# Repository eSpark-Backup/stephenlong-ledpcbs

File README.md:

# Direct Drive and Full Circuit LED Proto PCBAs
#### Client Name: Stephen Long Jr.

## Project Requirements
Refer to 2x2 design pushed in docs folder and carry out below requirements (the 2x2 design probably references more to the Full Circuit LED Proto PCBA)

### Full Circuit LED Proto PCBA
- Spaced 10mm center to center.
- Arranged in a 2 wide, 3 high grid.  

- UCS 7604 constant-current driver IC
- Required resistors, capacitors, and other supporting circuitry.
- Voltage VDD, GND, and data input/output lines will terminate in accessible solder pads for easy interfacing.
- The board should allow user to have both direct drive and full circuit capabilities by the following approach:
    - run each positive and negative pad to a row of jumpers, each LED will have 3 pins on this jumper header assigned to it. The center pin will be connected to the trace for the LED pad. The left pin will be connected to the full driving circuit with IC. The right pin will go directly to a solder pad. This sequence will happen for each led (x12), then:
        - **For Direct Drive:** User would put all the jumpers over to the center and right pin, then solder wires to the solder pads.
        - **For Full Circuit:** User would put all of the jumpers on the left and center pin for each LED.
- 4 x mounting holes for M3 screw clearance.

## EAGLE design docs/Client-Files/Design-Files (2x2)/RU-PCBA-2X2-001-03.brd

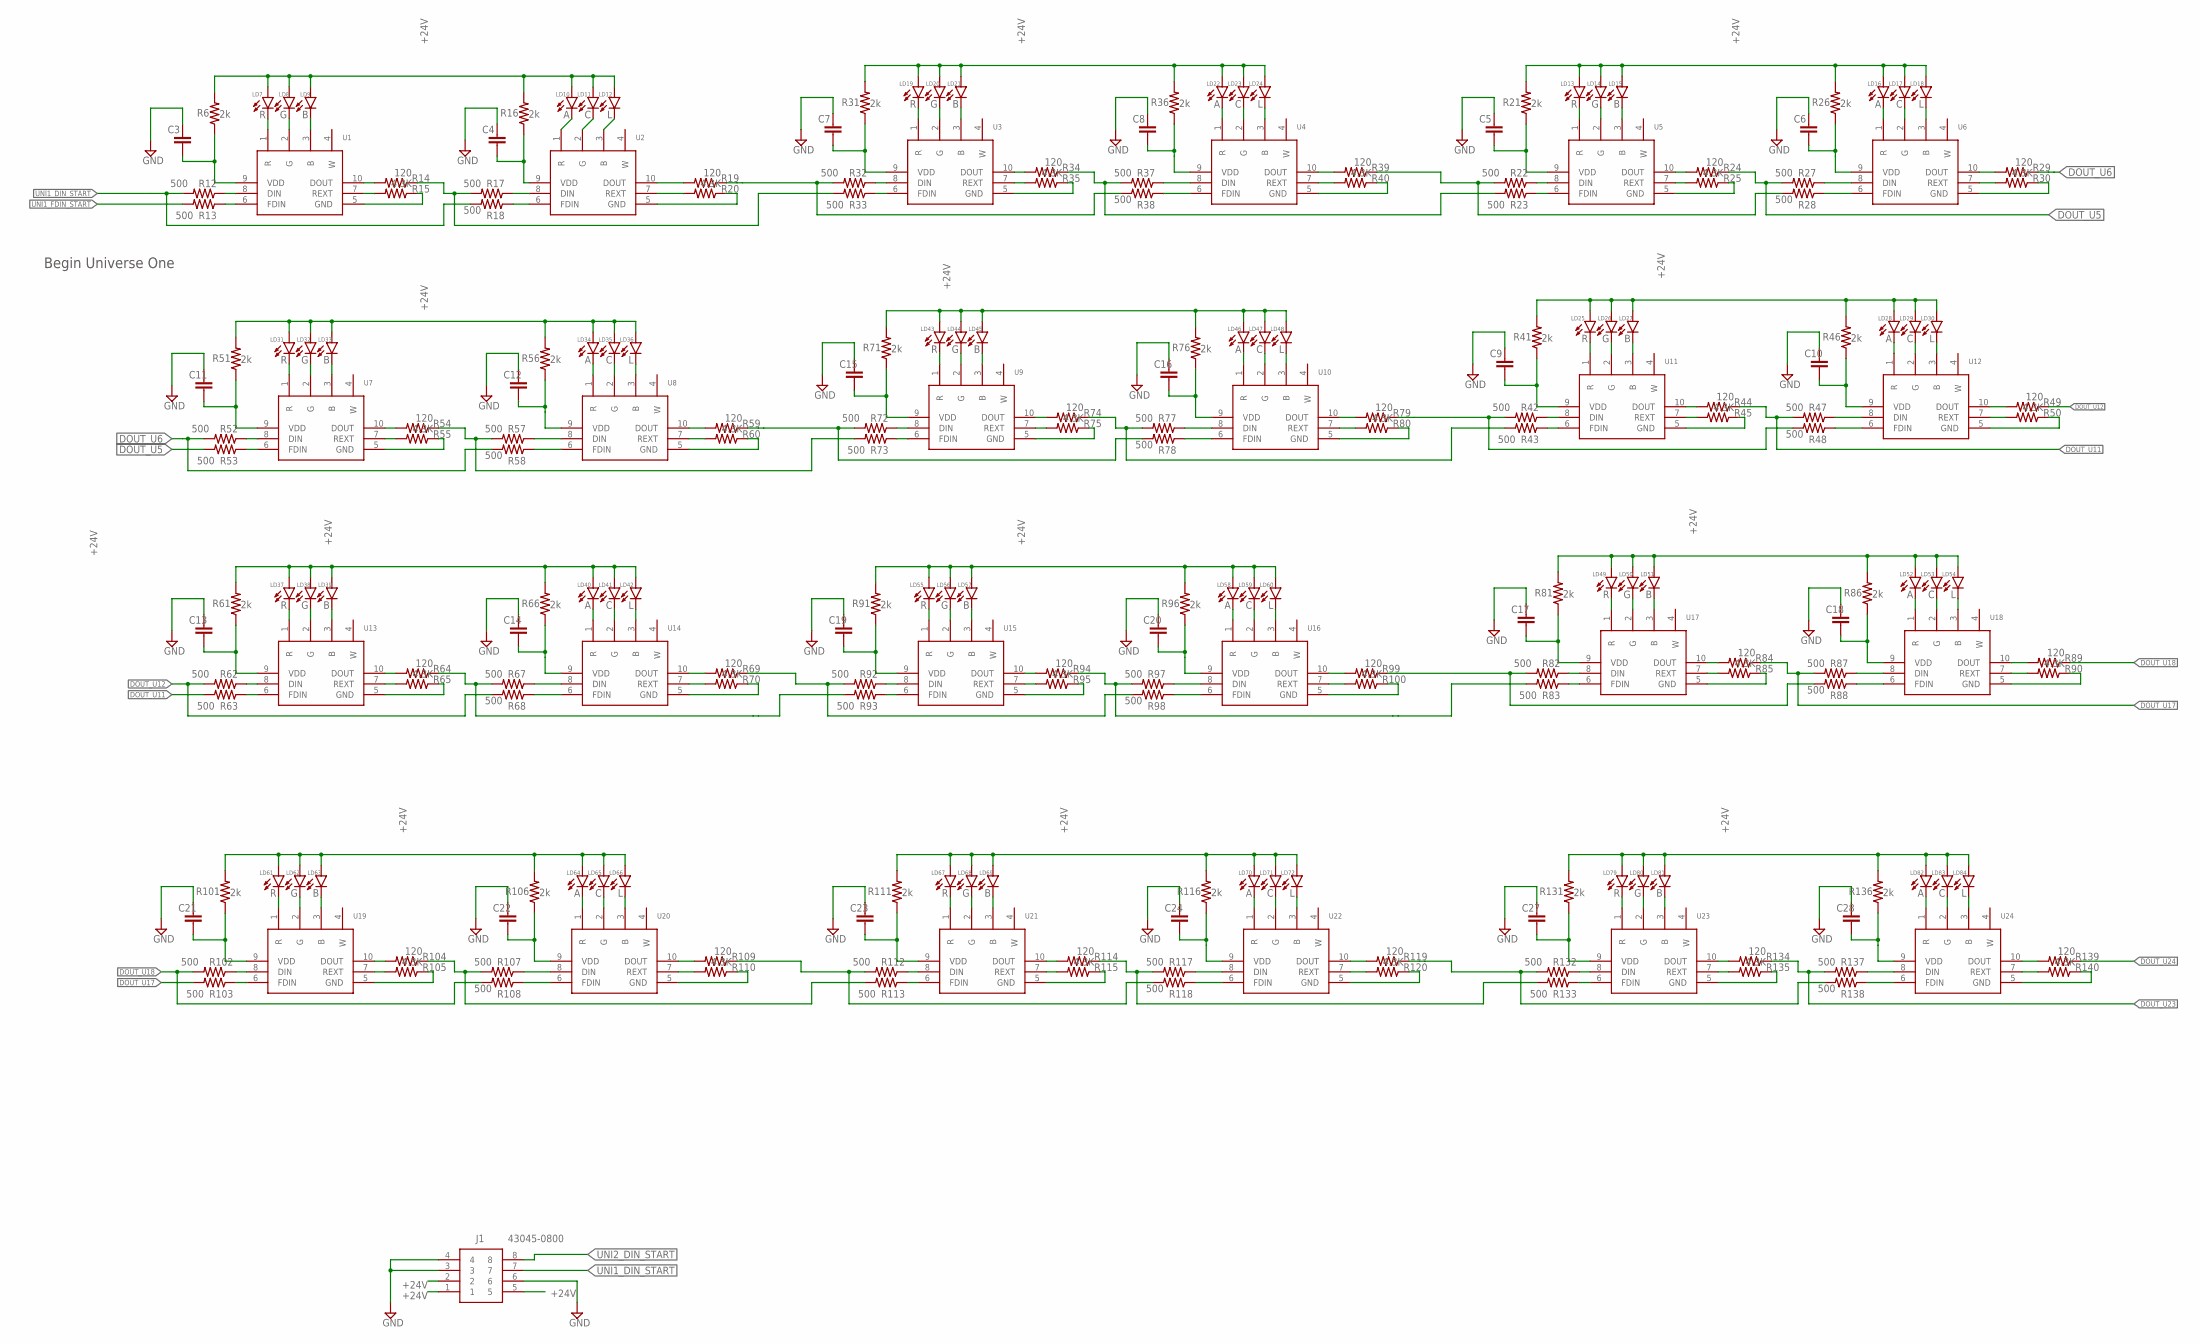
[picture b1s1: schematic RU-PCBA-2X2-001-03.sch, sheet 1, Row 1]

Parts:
C3, C4, C5, C6, C7, C8, C9, C10, C11, C12, C13, C14, C15, C16, C17, C18, C19, C20, C21, C22, C23, C24, C27, C28: C-EUC1206; C1206; MPN C_104
J1: 43045-0800; 43045-08(00,01,02,10)
LD7, LD13, LD19, LD25, LD31, LD37, LD43, LD49, LD55, LD61, LD67, LD79: R; 5050LED; MPN R_5050
LD8, LD14, LD20, LD26, LD32, LD38, LD44, LD50, LD56, LD62, LD68, LD80: G; 5050LED; MPN G_5050
LD9, LD15, LD21, LD27, LD33, LD39, LD45, LD51, LD57, LD63, LD69, LD81: B; 5050LED; MPN B_5050
LD10, LD16, LD22, LD28, LD34, LD40, LD46, LD52, LD58, LD64, LD70, LD82: A; 5050LED; MPN A_5050
LD11, LD17, LD23, LD29, LD35, LD41, LD47, LD53, LD59, LD65, LD71, LD83: C; 5050LED; MPN C_5050
LD12, LD18, LD24, LD30, LD36, LD42, LD48, LD54, LD60, LD66, LD72, LD84: L; 5050LED; MPN L_5050
R6, R16, R21, R26, R31, R36, R41, R46, R51, R56, R61, R66, R71, R76, R81, R86, R91, R96, R101, R106, R111, R116, R131, R136: 2k; R1206; MPN R_VDD
R12, R13, R17, R18, R22, R23, R27, R28, R32, R33, R37, R38, R42, R43, R47, R48, R52, R53, R57, R58, R62, R63, R67, R68, R72, R73, R77, R78, R82, R83, R87, R88, R92, R93, R97, R98, R102, R103, R107, R108, R112, R113, R117, R118, R132, R133, R137, R138: 500; R0805; MPN R_500
R14, R19, R24, R29, R34, R39, R44, R49, R54, R59, R64, R69, R74, R79, R84, R89, R94, R99, R104, R109, R114, R119, R134, R139: 120; R0805; MPN R_120
R15, R20, R25, R30, R35, R40, R45, R50, R55, R60, R65, R70, R75, R80, R85, R90, R95, R100, R105, R110, R115, R120, R135, R140: 4.3K; R0805; MPN R_EXT
U1, U2, U3, U4, U5, U6, U7, U8, U9, U10, U11, U12, U13, U14, U15, U16, U17, U18, U19, U20, U21, U22, U23, U24: UCS7604; SOP100P600X175-10N; MPN UCS7604

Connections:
+24V: J1.1, J1.2, J1.5, LD7.A, LD8.A, LD9.A, LD10.A, LD11.A, LD12.A, LD13.A, LD14.A, LD15.A, LD16.A, LD17.A, LD18.A, LD19.A, LD20.A, LD21.A, LD22.A, LD23.A, LD24.A, LD25.A, LD26.A, LD27.A, LD28.A, LD29.A, LD30.A, LD31.A, LD32.A, LD33.A, LD34.A, LD35.A, LD36.A, LD37.A, LD38.A, LD39.A, LD40.A, LD41.A, LD42.A, LD43.A, LD44.A, LD45.A, LD46.A, LD47.A, LD48.A, LD49.A, LD50.A, LD51.A, LD52.A, LD53.A, LD54.A, LD55.A, LD56.A, LD57.A, LD58.A, LD59.A, LD60.A, LD61.A, LD62.A, LD63.A, LD64.A, LD65.A, LD66.A, LD67.A, LD68.A, LD69.A, LD70.A, LD71.A, LD72.A, LD79.A, LD80.A, LD81.A, LD82.A, LD83.A, LD84.A, R6.2, R16.2, R21.2, R26.2, R31.2, R36.2, R41.2, R46.2, R51.2, R56.2, R61.2, R66.2, R71.2, R76.2, R81.2, R86.2, R91.2, R96.2, R101.2, R106.2, R111.2, R116.2, R131.2, R136.2; also elsewhere on the board
DOUT_U5: R24.1, R27.2, R53.2
DOUT_U6: R29.1, R52.2, R58.2
DOUT_U11: R44.1, R47.2, R63.2
DOUT_U12: R49.1, R62.2, R68.2
DOUT_U17: R84.1, R87.2, R103.2
DOUT_U18: R89.1, R102.2, R108.2
DOUT_U23: R134.1, R137.2; also elsewhere on the board
DOUT_U24: R139.1; also elsewhere on the board
GND: C3.2, C4.2, C5.2, C6.2, C7.2, C8.2, C9.2, C10.2, C11.2, C12.2, C13.2, C14.2, C15.2, C16.2, C17.2, C18.2, C19.2, C20.2, C21.2, C22.2, C23.2, C24.2, C27.2, C28.2, J1.3, J1.4, J1.6, R15.1, R20.1, R25.1, R30.1, R35.1, R40.1, R45.1, R50.1, R55.1, R60.1, R65.1, R70.1, R75.1, R80.1, R85.1, R90.1, R95.1, R100.1, R105.1, R110.1, R115.1, R120.1, R135.1, R140.1, U1.5 (GND), U2.5 (GND), U3.5 (GND), U4.5 (GND), U5.5 (GND), U6.5 (GND), U7.5 (GND), U8.5 (GND), U9.5 (GND), U10.5 (GND), U11.5 (GND), U12.5 (GND), U13.5 (GND), U14.5 (GND), U15.5 (GND), U16.5 (GND), U17.5 (GND), U18.5 (GND), U19.5 (GND), U20.5 (GND), U21.5 (GND), U22.5 (GND), U23.5 (GND), U24.5 (GND); also elsewhere on the board
unnamed: C3.1, R6.1, U1.9 (VDD)
unnamed: LD7.K (C), U1.1 (R)
unnamed: LD8.K (C), U1.2 (G)
unnamed: LD9.K (C), U1.3 (B)
unnamed: R12.1, U1.8 (DIN)
unnamed: R13.1, U1.6 (FDIN)
unnamed: R14.2, U1.10 (DOUT)
unnamed: R15.2, U1.7 (REXT)
unnamed: LD10.K (C), U2.1 (R)
unnamed: LD11.K (C), U2.2 (G)
unnamed: LD12.K (C), U2.3 (B)
unnamed: C4.1, R16.1, U2.9 (VDD)
unnamed: R17.1, U2.8 (DIN)
unnamed: R18.1, U2.6 (FDIN)
unnamed: R19.2, U2.10 (DOUT)
unnamed: R20.2, U2.7 (REXT)
unnamed: R19.1, R32.2, R38.2
unnamed: C5.1, R21.1, U5.9 (VDD)
unnamed: LD13.K (C), U5.1 (R)
unnamed: LD14.K (C), U5.2 (G)
unnamed: LD15.K (C), U5.3 (B)
unnamed: R22.1, U5.8 (DIN)
unnamed: R23.1, U5.6 (FDIN)
unnamed: R24.2, U5.10 (DOUT)
unnamed: R25.2, U5.7 (REXT)
unnamed: LD16.K (C), U6.1 (R)
unnamed: LD17.K (C), U6.2 (G)
unnamed: LD18.K (C), U6.3 (B)
unnamed: C6.1, R26.1, U6.9 (VDD)
unnamed: R27.1, U6.8 (DIN)
unnamed: R28.1, U6.6 (FDIN)
unnamed: R29.2, U6.10 (DOUT)
unnamed: R30.2, U6.7 (REXT)
unnamed: C7.1, R31.1, U3.9 (VDD)
unnamed: LD19.K (C), U3.1 (R)
unnamed: LD20.K (C), U3.2 (G)
unnamed: LD21.K (C), U3.3 (B)
unnamed: R32.1, U3.8 (DIN)
unnamed: R33.1, U3.6 (FDIN)
unnamed: R34.2, U3.10 (DOUT)
unnamed: R35.2, U3.7 (REXT)
unnamed: LD22.K (C), U4.1 (R)
unnamed: LD23.K (C), U4.2 (G)
unnamed: LD24.K (C), U4.3 (B)
unnamed: C8.1, R36.1, U4.9 (VDD)
unnamed: R37.1, U4.8 (DIN)
unnamed: R23.2, R34.1, R37.2
unnamed: R38.1, U4.6 (FDIN)
unnamed: R14.1, R17.2, R33.2
unnamed: R39.2, U4.10 (DOUT)
unnamed: R40.2, U4.7 (REXT)
unnamed: R22.2, R28.2, R39.1
unnamed: C9.1, R41.1, U11.9 (VDD)
unnamed: LD25.K (C), U11.1 (R)
unnamed: LD26.K (C), U11.2 (G)
unnamed: LD27.K (C), U11.3 (B)
unnamed: R42.1, U11.8 (DIN)
unnamed: R43.1, U11.6 (FDIN)
unnamed: R44.2, U11.10 (DOUT)
unnamed: R45.2, U11.7 (REXT)
unnamed: LD28.K (C), U12.1 (R)
unnamed: LD29.K (C), U12.2 (G)
unnamed: LD30.K (C), U12.3 (B)
unnamed: C10.1, R46.1, U12.9 (VDD)
unnamed: R47.1, U12.8 (DIN)
unnamed: R48.1, U12.6 (FDIN)
unnamed: R49.2, U12.10 (DOUT)
unnamed: R50.2, U12.7 (REXT)
unnamed: C11.1, R51.1, U7.9 (VDD)
unnamed: LD31.K (C), U7.1 (R)
unnamed: LD32.K (C), U7.2 (G)
unnamed: LD33.K (C), U7.3 (B)
unnamed: R52.1, U7.8 (DIN)
unnamed: R53.1, U7.6 (FDIN)
unnamed: R54.2, U7.10 (DOUT)
unnamed: R55.2, U7.7 (REXT)
unnamed: LD34.K (C), U8.1 (R)
unnamed: LD35.K (C), U8.2 (G)
unnamed: LD36.K (C), U8.3 (B)
unnamed: C12.1, R56.1, U8.9 (VDD)
unnamed: R57.1, U8.8 (DIN)
unnamed: R54.1, R57.2, R73.2
unnamed: R58.1, U8.6 (FDIN)
unnamed: R59.2, U8.10 (DOUT)
unnamed: R60.2, U8.7 (REXT)
unnamed: R59.1, R72.2, R78.2
unnamed: C13.1, R61.1, U13.9 (VDD)
unnamed: LD37.K (C), U13.1 (R)
unnamed: LD38.K (C), U13.2 (G)
unnamed: LD39.K (C), U13.3 (B)
unnamed: R62.1, U13.8 (DIN)
unnamed: R63.1, U13.6 (FDIN)
unnamed: R64.2, U13.10 (DOUT)
unnamed: R65.2, U13.7 (REXT)
unnamed: LD40.K (C), U14.1 (R)
unnamed: LD41.K (C), U14.2 (G)
unnamed: LD42.K (C), U14.3 (B)
unnamed: C14.1, R66.1, U14.9 (VDD)
unnamed: R67.1, U14.8 (DIN)
unnamed: R68.1, U14.6 (FDIN)
unnamed: R69.2, U14.10 (DOUT)
unnamed: R70.2, U14.7 (REXT)
unnamed: R69.1, R92.2, R98.2
unnamed: C15.1, R71.1, U9.9 (VDD)
unnamed: LD43.K (C), U9.1 (R)
unnamed: LD44.K (C), U9.2 (G)
unnamed: LD45.K (C), U9.3 (B)
unnamed: R72.1, U9.8 (DIN)
unnamed: R73.1, U9.6 (FDIN)
unnamed: R74.2, U9.10 (DOUT)
unnamed: R75.2, U9.7 (REXT)
unnamed: LD46.K (C), U10.1 (R)
unnamed: LD47.K (C), U10.2 (G)
unnamed: LD48.K (C), U10.3 (B)
unnamed: C16.1, R76.1, U10.9 (VDD)
unnamed: R77.1, U10.8 (DIN)
unnamed: R43.2, R74.1, R77.2
unnamed: R78.1, U10.6 (FDIN)
unnamed: R79.2, U10.10 (DOUT)
unnamed: R80.2, U10.7 (REXT)
unnamed: R42.2, R48.2, R79.1
unnamed: C17.1, R81.1, U17.9 (VDD)
unnamed: LD49.K (C), U17.1 (R)
unnamed: LD50.K (C), U17.2 (G)
unnamed: LD51.K (C), U17.3 (B)
unnamed: R82.1, U17.8 (DIN)
unnamed: R83.1, U17.6 (FDIN)
unnamed: R84.2, U17.10 (DOUT)
unnamed: R85.2, U17.7 (REXT)
unnamed: LD52.K (C), U18.1 (R)
unnamed: LD53.K (C), U18.2 (G)
unnamed: LD54.K (C), U18.3 (B)
unnamed: C18.1, R86.1, U18.9 (VDD)
unnamed: R87.1, U18.8 (DIN)
unnamed: R88.1, U18.6 (FDIN)
unnamed: R82.2, R88.2, R99.1
unnamed: R83.2, R94.1, R97.2
unnamed: R89.2, U18.10 (DOUT)
unnamed: R90.2, U18.7 (REXT)
unnamed: C19.1, R91.1, U15.9 (VDD)
unnamed: LD55.K (C), U15.1 (R)
unnamed: LD56.K (C), U15.2 (G)
unnamed: LD57.K (C), U15.3 (B)
unnamed: R92.1, U15.8 (DIN)
unnamed: R93.1, U15.6 (FDIN)
unnamed: R94.2, U15.10 (DOUT)
unnamed: R95.2, U15.7 (REXT)
unnamed: LD58.K (C), U16.1 (R)
unnamed: LD59.K (C), U16.2 (G)
unnamed: LD60.K (C), U16.3 (B)
unnamed: C20.1, R96.1, U16.9 (VDD)
unnamed: R97.1, U16.8 (DIN)
unnamed: R98.1, U16.6 (FDIN)
unnamed: R64.1, R67.2, R93.2
unnamed: R99.2, U16.10 (DOUT)
unnamed: R100.2, U16.7 (REXT)
unnamed: C21.1, R101.1, U19.9 (VDD)
unnamed: LD61.K (C), U19.1 (R)
unnamed: LD62.K (C), U19.2 (G)
unnamed: LD63.K (C), U19.3 (B)
unnamed: R102.1, U19.8 (DIN)
unnamed: R103.1, U19.6 (FDIN)
unnamed: R104.2, U19.10 (DOUT)
unnamed: R105.2, U19.7 (REXT)
unnamed: LD64.K (C), U20.1 (R)
unnamed: LD65.K (C), U20.2 (G)
unnamed: LD66.K (C), U20.3 (B)
unnamed: C22.1, R106.1, U20.9 (VDD)
unnamed: R107.1, U20.8 (DIN)
unnamed: R104.1, R107.2, R113.2
unnamed: R108.1, U20.6 (FDIN)
unnamed: R109.2, U20.10 (DOUT)
unnamed: R110.2, U20.7 (REXT)
unnamed: R109.1, R112.2, R118.2
unnamed: C23.1, R111.1, U21.9 (VDD)
unnamed: LD67.K (C), U21.1 (R)
unnamed: LD68.K (C), U21.2 (G)
unnamed: LD69.K (C), U21.3 (B)
unnamed: R112.1, U21.8 (DIN)
unnamed: R113.1, U21.6 (FDIN)
unnamed: R114.2, U21.10 (DOUT)
unnamed: R115.2, U21.7 (REXT)
unnamed: LD70.K (C), U22.1 (R)
unnamed: LD71.K (C), U22.2 (G)
unnamed: LD72.K (C), U22.3 (B)
unnamed: C24.1, R116.1, U22.9 (VDD)
unnamed: R117.1, U22.8 (DIN)
unnamed: R114.1, R117.2, R133.2
unnamed: R118.1, U22.6 (FDIN)
unnamed: R119.2, U22.10 (DOUT)
unnamed: R120.2, U22.7 (REXT)
unnamed: C27.1, R131.1, U23.9 (VDD)
unnamed: LD79.K (C), U23.1 (R)
unnamed: LD80.K (C), U23.2 (G)
unnamed: LD81.K (C), U23.3 (B)
unnamed: R132.1, U23.8 (DIN)
unnamed: R133.1, U23.6 (FDIN)
unnamed: R134.2, U23.10 (DOUT)
unnamed: R135.2, U23.7 (REXT)
unnamed: LD82.K (C), U24.1 (R)
unnamed: LD83.K (C), U24.2 (G)
unnamed: LD84.K (C), U24.3 (B)
unnamed: C28.1, R136.1, U24.9 (VDD)
unnamed: R137.1, U24.8 (DIN)
unnamed: R138.1, U24.6 (FDIN)
unnamed: R119.1, R132.2, R138.2
unnamed: R139.2, U24.10 (DOUT)
unnamed: R140.2, U24.7 (REXT)
UNI1_DIN_START: J1.7, R12.2, R18.2
UNI1_FDIN_START: R13.2
UNI2_DIN_START: J1.8; also elsewhere on the board

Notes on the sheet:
Begin Universe One

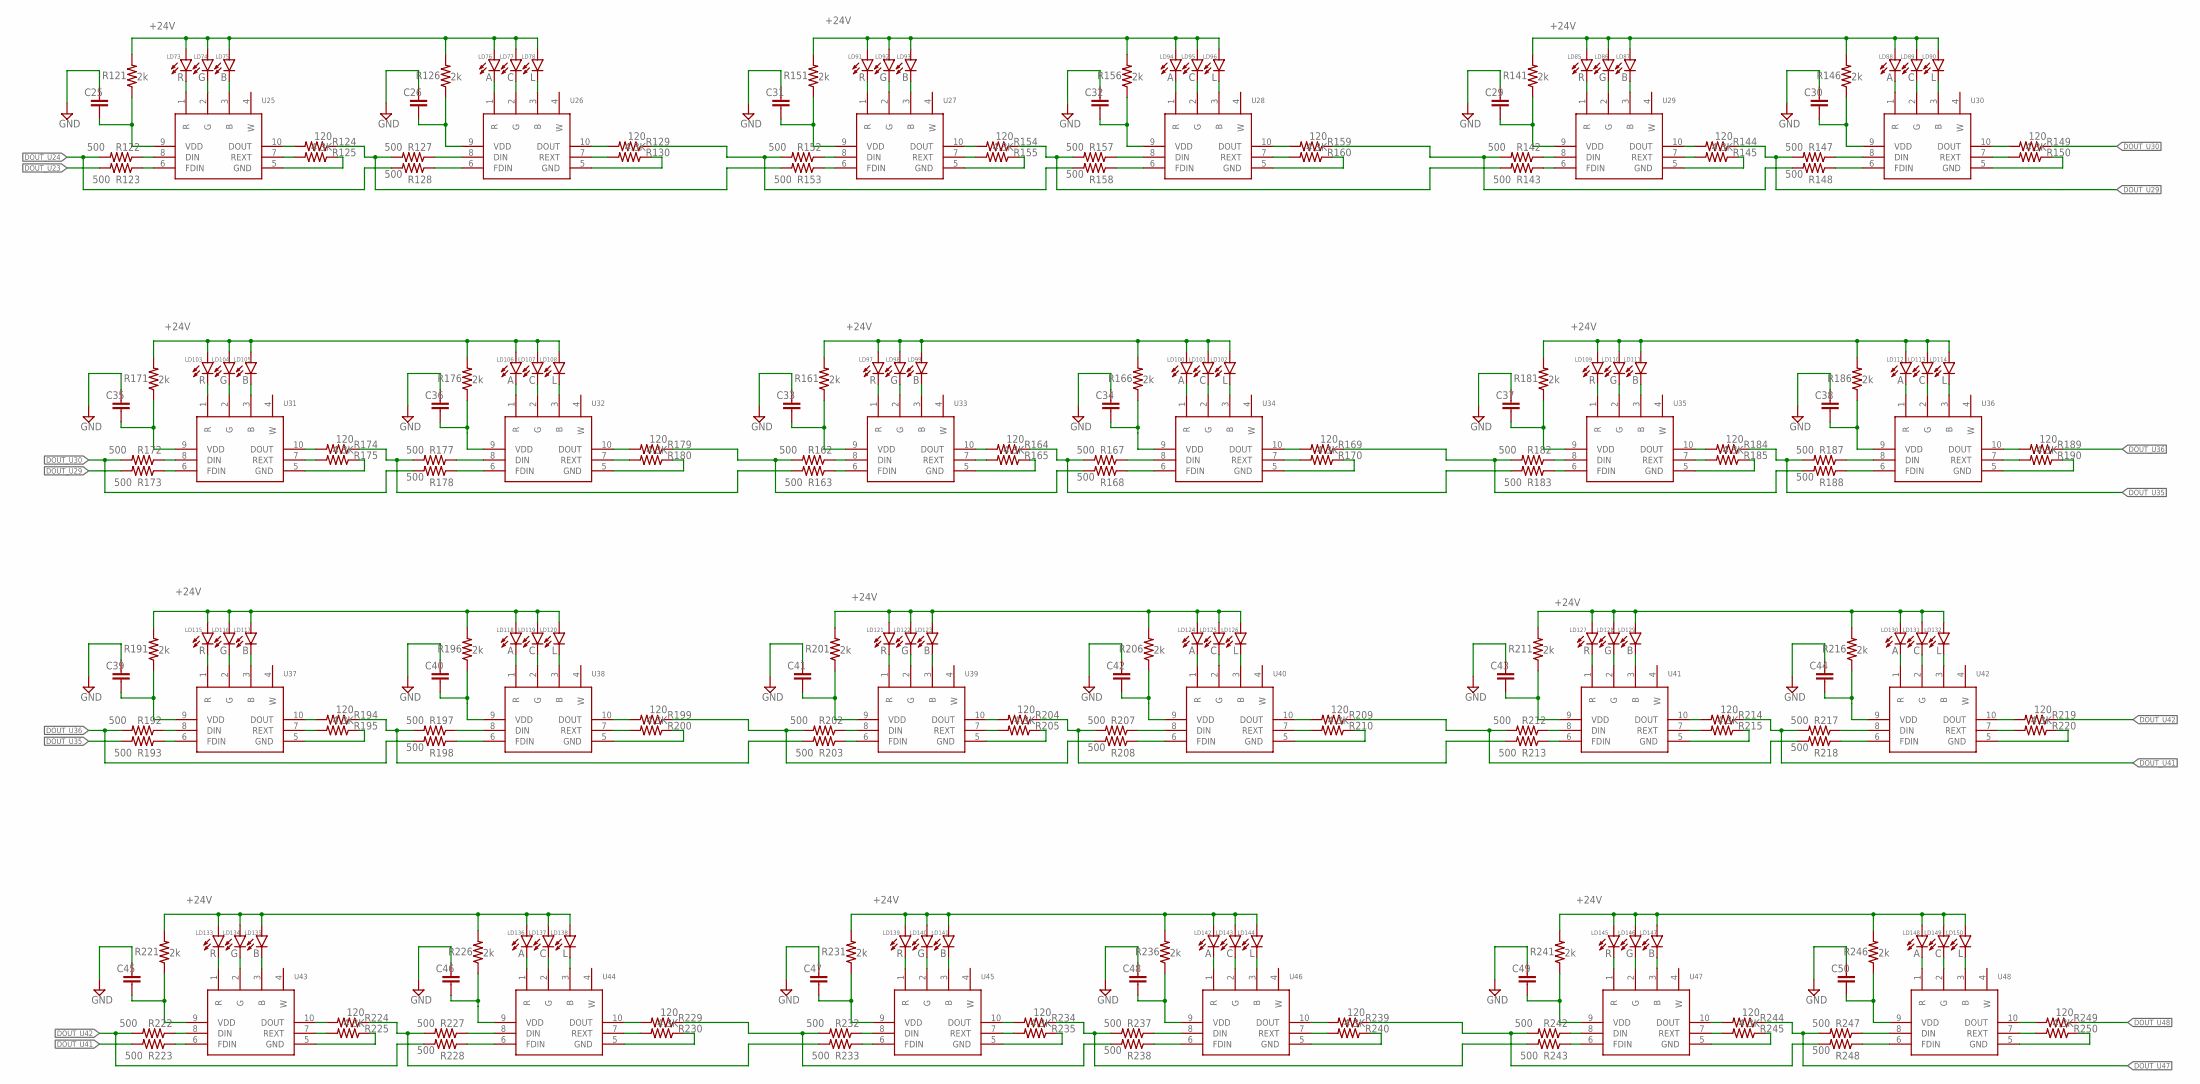
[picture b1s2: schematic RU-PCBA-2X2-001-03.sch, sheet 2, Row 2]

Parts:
C25, C26, C29, C30, C31, C32, C33, C34, C35, C36, C37, C38, C39, C40, C41, C42, C43, C44, C45, C46, C47, C48, C49, C50: C-EUC1206; C1206; MPN C_104
LD73, LD85, LD91, LD97, LD103, LD109, LD115, LD121, LD127, LD133, LD139, LD145: R; 5050LED; MPN R_5050
LD74, LD86, LD92, LD98, LD104, LD110, LD116, LD122, LD128, LD134, LD140, LD146: G; 5050LED; MPN G_5050
LD75, LD87, LD93, LD99, LD105, LD111, LD117, LD123, LD129, LD135, LD141, LD147: B; 5050LED; MPN B_5050
LD76, LD88, LD94, LD100, LD106, LD112, LD118, LD124, LD130, LD136, LD142, LD148: A; 5050LED; MPN A_5050
LD77, LD89, LD95, LD101, LD107, LD113, LD119, LD125, LD131, LD137, LD143, LD149: C; 5050LED; MPN C_5050
LD78, LD90, LD96, LD102, LD108, LD114, LD120, LD126, LD132, LD138, LD144, LD150: L; 5050LED; MPN L_5050
R121, R126, R141, R146, R151, R156, R161, R166, R171, R176, R181, R186, R191, R196, R201, R206, R211, R216, R221, R226, R231, R236, R241, R246: 2k; R1206; MPN R_VDD
R122, R123, R127, R128, R142, R143, R147, R148, R152, R153, R157, R158, R162, R163, R167, R168, R172, R173, R177, R178, R182, R183, R187, R188, R192, R193, R197, R198, R202, R203, R207, R208, R212, R213, R217, R218, R222, R223, R227, R228, R232, R233, R237, R238, R242, R243, R247, R248: 500; R0805; MPN R_500
R124, R129, R144, R149, R154, R159, R164, R169, R174, R179, R184, R189, R194, R199, R204, R209, R214, R219, R224, R229, R234, R239, R244, R249: 120; R0805; MPN R_120
R125, R130, R145, R150, R155, R160, R165, R170, R175, R180, R185, R190, R195, R200, R205, R210, R215, R220, R225, R230, R235, R240, R245, R250: 4.3K; R0805; MPN R_EXT
U25, U26, U27, U28, U29, U30, U31, U32, U33, U34, U35, U36, U37, U38, U39, U40, U41, U42, U43, U44, U45, U46, U47, U48: UCS7604; SOP100P600X175-10N; MPN UCS7604

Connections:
+24V: LD73.A, LD74.A, LD75.A, LD76.A, LD77.A, LD78.A, LD85.A, LD86.A, LD87.A, LD88.A, LD89.A, LD90.A, LD91.A, LD92.A, LD93.A, LD94.A, LD95.A, LD96.A, LD97.A, LD98.A, LD99.A, LD100.A, LD101.A, LD102.A, LD103.A, LD104.A, LD105.A, LD106.A, LD107.A, LD108.A, LD109.A, LD110.A, LD111.A, LD112.A, LD113.A, LD114.A, LD115.A, LD116.A, LD117.A, LD118.A, LD119.A, LD120.A, LD121.A, LD122.A, LD123.A, LD124.A, LD125.A, LD126.A, LD127.A, LD128.A, LD129.A, LD130.A, LD131.A, LD132.A, LD133.A, LD134.A, LD135.A, LD136.A, LD137.A, LD138.A, LD139.A, LD140.A, LD141.A, LD142.A, LD143.A, LD144.A, LD145.A, LD146.A, LD147.A, LD148.A, LD149.A, LD150.A, R121.2, R126.2, R141.2, R146.2, R151.2, R156.2, R161.2, R166.2, R171.2, R176.2, R181.2, R186.2, R191.2, R196.2, R201.2, R206.2, R211.2, R216.2, R221.2, R226.2, R231.2, R236.2, R241.2, R246.2; also elsewhere on the board
DOUT_U23: R123.2; also elsewhere on the board
DOUT_U24: R122.2, R128.2; also elsewhere on the board
DOUT_U29: R144.1, R147.2, R173.2
DOUT_U30: R149.1, R172.2, R178.2
DOUT_U35: R184.1, R187.2, R193.2
DOUT_U36: R189.1, R192.2, R198.2
DOUT_U41: R214.1, R217.2, R223.2
DOUT_U42: R219.1, R222.2, R228.2
DOUT_U47: R244.1, R247.2; also elsewhere on the board
DOUT_U48: R249.1; also elsewhere on the board
GND: C25.2, C26.2, C29.2, C30.2, C31.2, C32.2, C33.2, C34.2, C35.2, C36.2, C37.2, C38.2, C39.2, C40.2, C41.2, C42.2, C43.2, C44.2, C45.2, C46.2, C47.2, C48.2, C49.2, C50.2, R125.1, R130.1, R145.1, R150.1, R155.1, R160.1, R165.1, R170.1, R175.1, R180.1, R185.1, R190.1, R195.1, R200.1, R205.1, R210.1, R215.1, R220.1, R225.1, R230.1, R235.1, R240.1, R245.1, R250.1, U25.5 (GND), U26.5 (GND), U27.5 (GND), U28.5 (GND), U29.5 (GND), U30.5 (GND), U31.5 (GND), U32.5 (GND), U33.5 (GND), U34.5 (GND), U35.5 (GND), U36.5 (GND), U37.5 (GND), U38.5 (GND), U39.5 (GND), U40.5 (GND), U41.5 (GND), U42.5 (GND), U43.5 (GND), U44.5 (GND), U45.5 (GND), U46.5 (GND), U47.5 (GND), U48.5 (GND); also elsewhere on the board
unnamed: C25.1, R121.1, U25.9 (VDD)
unnamed: LD73.K (C), U25.1 (R)
unnamed: LD74.K (C), U25.2 (G)
unnamed: LD75.K (C), U25.3 (B)
unnamed: R122.1, U25.8 (DIN)
unnamed: R123.1, U25.6 (FDIN)
unnamed: R124.2, U25.10 (DOUT)
unnamed: R125.2, U25.7 (REXT)
unnamed: LD76.K (C), U26.1 (R)
unnamed: LD77.K (C), U26.2 (G)
unnamed: LD78.K (C), U26.3 (B)
unnamed: C26.1, R126.1, U26.9 (VDD)
unnamed: R127.1, U26.8 (DIN)
unnamed: R128.1, U26.6 (FDIN)
unnamed: R129.2, U26.10 (DOUT)
unnamed: R130.2, U26.7 (REXT)
unnamed: R129.1, R152.2, R158.2
unnamed: C29.1, R141.1, U29.9 (VDD)
unnamed: LD85.K (C), U29.1 (R)
unnamed: LD86.K (C), U29.2 (G)
unnamed: LD87.K (C), U29.3 (B)
unnamed: R142.1, U29.8 (DIN)
unnamed: R143.1, U29.6 (FDIN)
unnamed: R144.2, U29.10 (DOUT)
unnamed: R145.2, U29.7 (REXT)
unnamed: LD88.K (C), U30.1 (R)
unnamed: LD89.K (C), U30.2 (G)
unnamed: LD90.K (C), U30.3 (B)
unnamed: C30.1, R146.1, U30.9 (VDD)
unnamed: R147.1, U30.8 (DIN)
unnamed: R148.1, U30.6 (FDIN)
unnamed: R143.2, R154.1, R157.2
unnamed: R149.2, U30.10 (DOUT)
unnamed: R150.2, U30.7 (REXT)
unnamed: C31.1, R151.1, U27.9 (VDD)
unnamed: LD91.K (C), U27.1 (R)
unnamed: LD92.K (C), U27.2 (G)
unnamed: LD93.K (C), U27.3 (B)
unnamed: R152.1, U27.8 (DIN)
unnamed: R153.1, U27.6 (FDIN)
unnamed: R154.2, U27.10 (DOUT)
unnamed: R155.2, U27.7 (REXT)
unnamed: LD94.K (C), U28.1 (R)
unnamed: LD95.K (C), U28.2 (G)
unnamed: LD96.K (C), U28.3 (B)
unnamed: C32.1, R156.1, U28.9 (VDD)
unnamed: R157.1, U28.8 (DIN)
unnamed: R158.1, U28.6 (FDIN)
unnamed: R124.1, R127.2, R153.2
unnamed: R159.2, U28.10 (DOUT)
unnamed: R160.2, U28.7 (REXT)
unnamed: R142.2, R148.2, R159.1
unnamed: C33.1, R161.1, U33.9 (VDD)
unnamed: LD97.K (C), U33.1 (R)
unnamed: LD98.K (C), U33.2 (G)
unnamed: LD99.K (C), U33.3 (B)
unnamed: R162.1, U33.8 (DIN)
unnamed: R163.1, U33.6 (FDIN)
unnamed: R164.2, U33.10 (DOUT)
unnamed: R165.2, U33.7 (REXT)
unnamed: LD100.K (C), U34.1 (R)
unnamed: LD101.K (C), U34.2 (G)
unnamed: LD102.K (C), U34.3 (B)
unnamed: C34.1, R166.1, U34.9 (VDD)
unnamed: R167.1, U34.8 (DIN)
unnamed: R168.1, U34.6 (FDIN)
unnamed: R163.2, R174.1, R177.2
unnamed: R169.2, U34.10 (DOUT)
unnamed: R170.2, U34.7 (REXT)
unnamed: R169.1, R182.2, R188.2
unnamed: C35.1, R171.1, U31.9 (VDD)
unnamed: LD103.K (C), U31.1 (R)
unnamed: LD104.K (C), U31.2 (G)
unnamed: LD105.K (C), U31.3 (B)
unnamed: R172.1, U31.8 (DIN)
unnamed: R173.1, U31.6 (FDIN)
unnamed: R174.2, U31.10 (DOUT)
unnamed: R175.2, U31.7 (REXT)
unnamed: LD106.K (C), U32.1 (R)
unnamed: LD107.K (C), U32.2 (G)
unnamed: LD108.K (C), U32.3 (B)
unnamed: C36.1, R176.1, U32.9 (VDD)
unnamed: R177.1, U32.8 (DIN)
unnamed: R178.1, U32.6 (FDIN)
unnamed: R179.2, U32.10 (DOUT)
unnamed: R180.2, U32.7 (REXT)
unnamed: R162.2, R168.2, R179.1
unnamed: C37.1, R181.1, U35.9 (VDD)
unnamed: LD109.K (C), U35.1 (R)
unnamed: LD110.K (C), U35.2 (G)
unnamed: LD111.K (C), U35.3 (B)
unnamed: R182.1, U35.8 (DIN)
unnamed: R183.1, U35.6 (FDIN)
unnamed: R184.2, U35.10 (DOUT)
unnamed: R185.2, U35.7 (REXT)
unnamed: LD112.K (C), U36.1 (R)
unnamed: LD113.K (C), U36.2 (G)
unnamed: LD114.K (C), U36.3 (B)
unnamed: C38.1, R186.1, U36.9 (VDD)
unnamed: R187.1, U36.8 (DIN)
unnamed: R188.1, U36.6 (FDIN)
unnamed: R164.1, R167.2, R183.2
unnamed: R189.2, U36.10 (DOUT)
unnamed: R190.2, U36.7 (REXT)
unnamed: C39.1, R191.1, U37.9 (VDD)
unnamed: LD115.K (C), U37.1 (R)
unnamed: LD116.K (C), U37.2 (G)
unnamed: LD117.K (C), U37.3 (B)
unnamed: R192.1, U37.8 (DIN)
unnamed: R193.1, U37.6 (FDIN)
unnamed: R194.2, U37.10 (DOUT)
unnamed: R195.2, U37.7 (REXT)
unnamed: LD118.K (C), U38.1 (R)
unnamed: LD119.K (C), U38.2 (G)
unnamed: LD120.K (C), U38.3 (B)
unnamed: C40.1, R196.1, U38.9 (VDD)
unnamed: R197.1, U38.8 (DIN)
unnamed: R198.1, U38.6 (FDIN)
unnamed: R199.2, U38.10 (DOUT)
unnamed: R200.2, U38.7 (REXT)
unnamed: R199.1, R202.2, R208.2
unnamed: C41.1, R201.1, U39.9 (VDD)
unnamed: LD121.K (C), U39.1 (R)
unnamed: LD122.K (C), U39.2 (G)
unnamed: LD123.K (C), U39.3 (B)
unnamed: R202.1, U39.8 (DIN)
unnamed: R203.1, U39.6 (FDIN)
unnamed: R204.2, U39.10 (DOUT)
unnamed: R205.2, U39.7 (REXT)
unnamed: LD124.K (C), U40.1 (R)
unnamed: LD125.K (C), U40.2 (G)
unnamed: LD126.K (C), U40.3 (B)
unnamed: C42.1, R206.1, U40.9 (VDD)
unnamed: R207.1, U40.8 (DIN)
unnamed: R208.1, U40.6 (FDIN)
unnamed: R194.1, R197.2, R203.2
unnamed: R209.2, U40.10 (DOUT)
unnamed: R210.2, U40.7 (REXT)
unnamed: R209.1, R212.2, R218.2
unnamed: C43.1, R211.1, U41.9 (VDD)
unnamed: LD127.K (C), U41.1 (R)
unnamed: LD128.K (C), U41.2 (G)
unnamed: LD129.K (C), U41.3 (B)
unnamed: R212.1, U41.8 (DIN)
unnamed: R213.1, U41.6 (FDIN)
unnamed: R214.2, U41.10 (DOUT)
unnamed: R215.2, U41.7 (REXT)
unnamed: LD130.K (C), U42.1 (R)
unnamed: LD131.K (C), U42.2 (G)
unnamed: LD132.K (C), U42.3 (B)
unnamed: C44.1, R216.1, U42.9 (VDD)
unnamed: R217.1, U42.8 (DIN)
unnamed: R218.1, U42.6 (FDIN)
unnamed: R204.1, R207.2, R213.2
unnamed: R219.2, U42.10 (DOUT)
unnamed: R220.2, U42.7 (REXT)
unnamed: C45.1, R221.1, U43.9 (VDD)
unnamed: LD133.K (C), U43.1 (R)
unnamed: LD134.K (C), U43.2 (G)
unnamed: LD135.K (C), U43.3 (B)
unnamed: R222.1, U43.8 (DIN)
unnamed: R223.1, U43.6 (FDIN)
unnamed: R224.2, U43.10 (DOUT)
unnamed: R225.2, U43.7 (REXT)
unnamed: LD136.K (C), U44.1 (R)
unnamed: LD137.K (C), U44.2 (G)
unnamed: LD138.K (C), U44.3 (B)
unnamed: C46.1, R226.1, U44.9 (VDD)
unnamed: R227.1, U44.8 (DIN)
unnamed: R228.1, U44.6 (FDIN)
unnamed: R229.2, U44.10 (DOUT)
unnamed: R230.2, U44.7 (REXT)
unnamed: R229.1, R232.2, R238.2
unnamed: C47.1, R231.1, U45.9 (VDD)
unnamed: LD139.K (C), U45.1 (R)
unnamed: LD140.K (C), U45.2 (G)
unnamed: LD141.K (C), U45.3 (B)
unnamed: R232.1, U45.8 (DIN)
unnamed: R233.1, U45.6 (FDIN)
unnamed: R234.2, U45.10 (DOUT)
unnamed: R235.2, U45.7 (REXT)
unnamed: LD142.K (C), U46.1 (R)
unnamed: LD143.K (C), U46.2 (G)
unnamed: LD144.K (C), U46.3 (B)
unnamed: C48.1, R236.1, U46.9 (VDD)
unnamed: R237.1, U46.8 (DIN)
unnamed: R238.1, U46.6 (FDIN)
unnamed: R224.1, R227.2, R233.2
unnamed: R239.2, U46.10 (DOUT)
unnamed: R240.2, U46.7 (REXT)
unnamed: R239.1, R242.2, R248.2
unnamed: C49.1, R241.1, U47.9 (VDD)
unnamed: LD145.K (C), U47.1 (R)
unnamed: LD146.K (C), U47.2 (G)
unnamed: LD147.K (C), U47.3 (B)
unnamed: R242.1, U47.8 (DIN)
unnamed: R243.1, U47.6 (FDIN)
unnamed: R244.2, U47.10 (DOUT)
unnamed: R245.2, U47.7 (REXT)
unnamed: LD148.K (C), U48.1 (R)
unnamed: LD149.K (C), U48.2 (G)
unnamed: LD150.K (C), U48.3 (B)
unnamed: C50.1, R246.1, U48.9 (VDD)
unnamed: R247.1, U48.8 (DIN)
unnamed: R248.1, U48.6 (FDIN)
unnamed: R234.1, R237.2, R243.2
unnamed: R249.2, U48.10 (DOUT)
unnamed: R250.2, U48.7 (REXT)
